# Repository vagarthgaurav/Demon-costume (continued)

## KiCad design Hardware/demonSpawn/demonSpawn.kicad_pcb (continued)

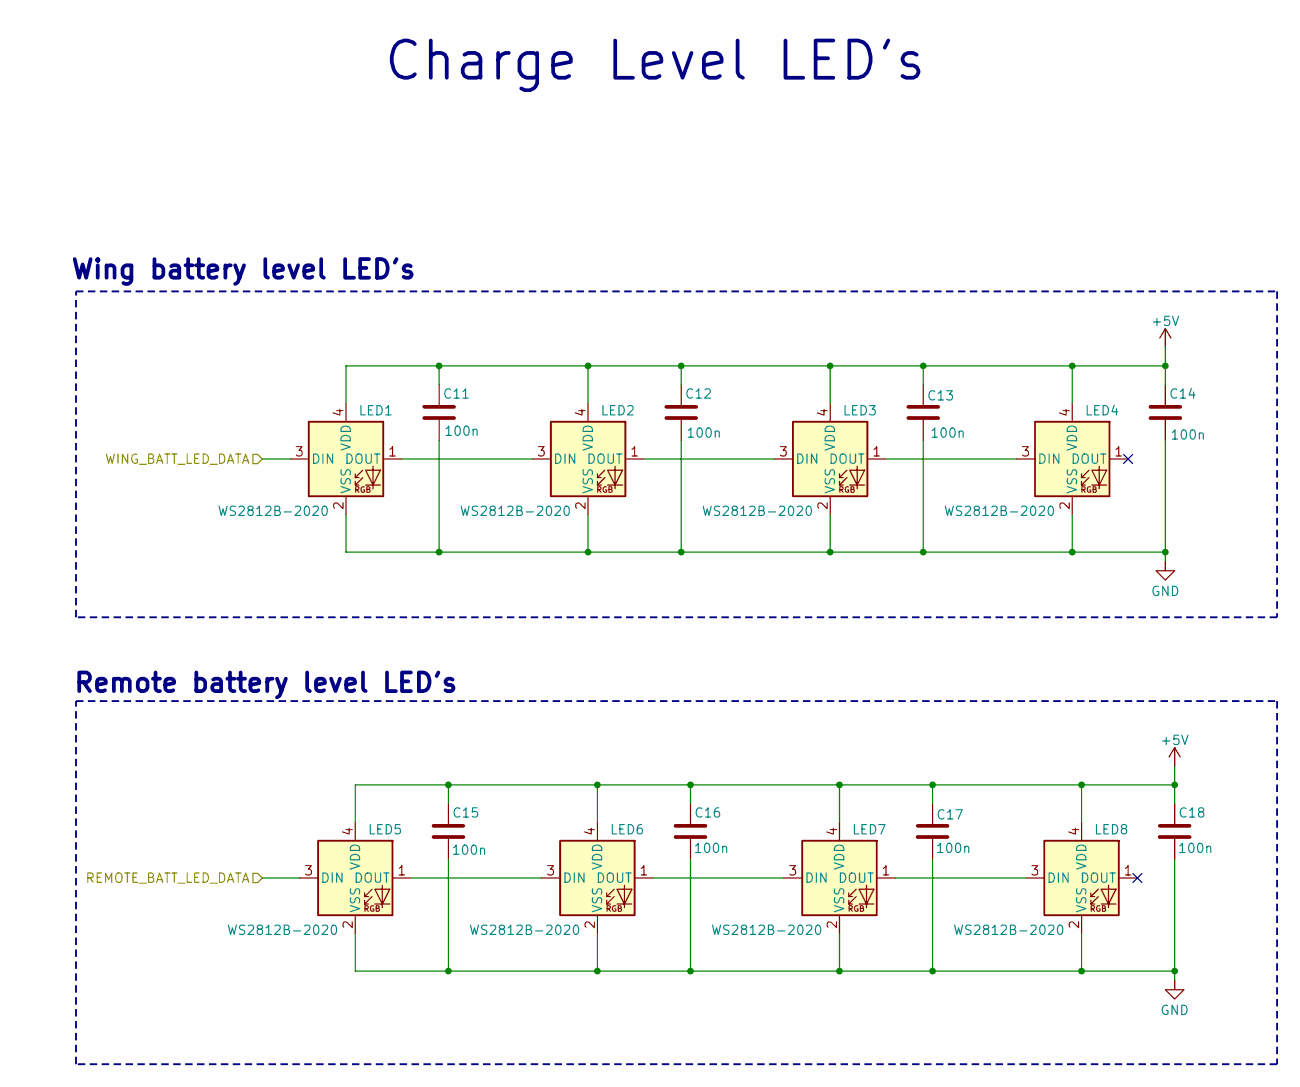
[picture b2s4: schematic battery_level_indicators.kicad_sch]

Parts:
C11, C12, C13, C14, C15, C16, C17, C18: 100n; C_0402_1005Metric
LED1, LED2, LED3, LED4, LED5, LED6, LED7, LED8: WS2812B-2020; LED_WS2812B-2020_PLCC4_2.0x2.0mm

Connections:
+5V: C11.2, C12.2, C13.2, C14.2, C15.2, C16.2, C17.2, C18.2, LED1.4 (VDD), LED2.4 (VDD), LED3.4 (VDD), LED4.4 (VDD), LED5.4 (VDD), LED6.4 (VDD), LED7.4 (VDD), LED8.4 (VDD); also elsewhere on the board
/Battery Level Indicators/REMOTE_BATT_LED_DATA: LED5.3 (DIN); also elsewhere on the board
/Battery Level Indicators/WING_BATT_LED_DATA: LED1.3 (DIN); also elsewhere on the board
GND: C11.1, C12.1, C13.1, C14.1, C15.1, C16.1, C17.1, C18.1, LED1.2 (VSS), LED2.2 (VSS), LED3.2 (VSS), LED4.2 (VSS), LED5.2 (VSS), LED6.2 (VSS), LED7.2 (VSS), LED8.2 (VSS); also elsewhere on the board
unnamed: LED1.1 (DOUT), LED2.3 (DIN)
unnamed: LED2.1 (DOUT), LED3.3 (DIN)
unnamed: LED3.1 (DOUT), LED4.3 (DIN)
unnamed: LED5.1 (DOUT), LED6.3 (DIN)
unnamed: LED6.1 (DOUT), LED7.3 (DIN)
unnamed: LED7.1 (DOUT), LED8.3 (DIN)

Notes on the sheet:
Charge Level LED's
Wing battery level LED's
Remote battery level LED's

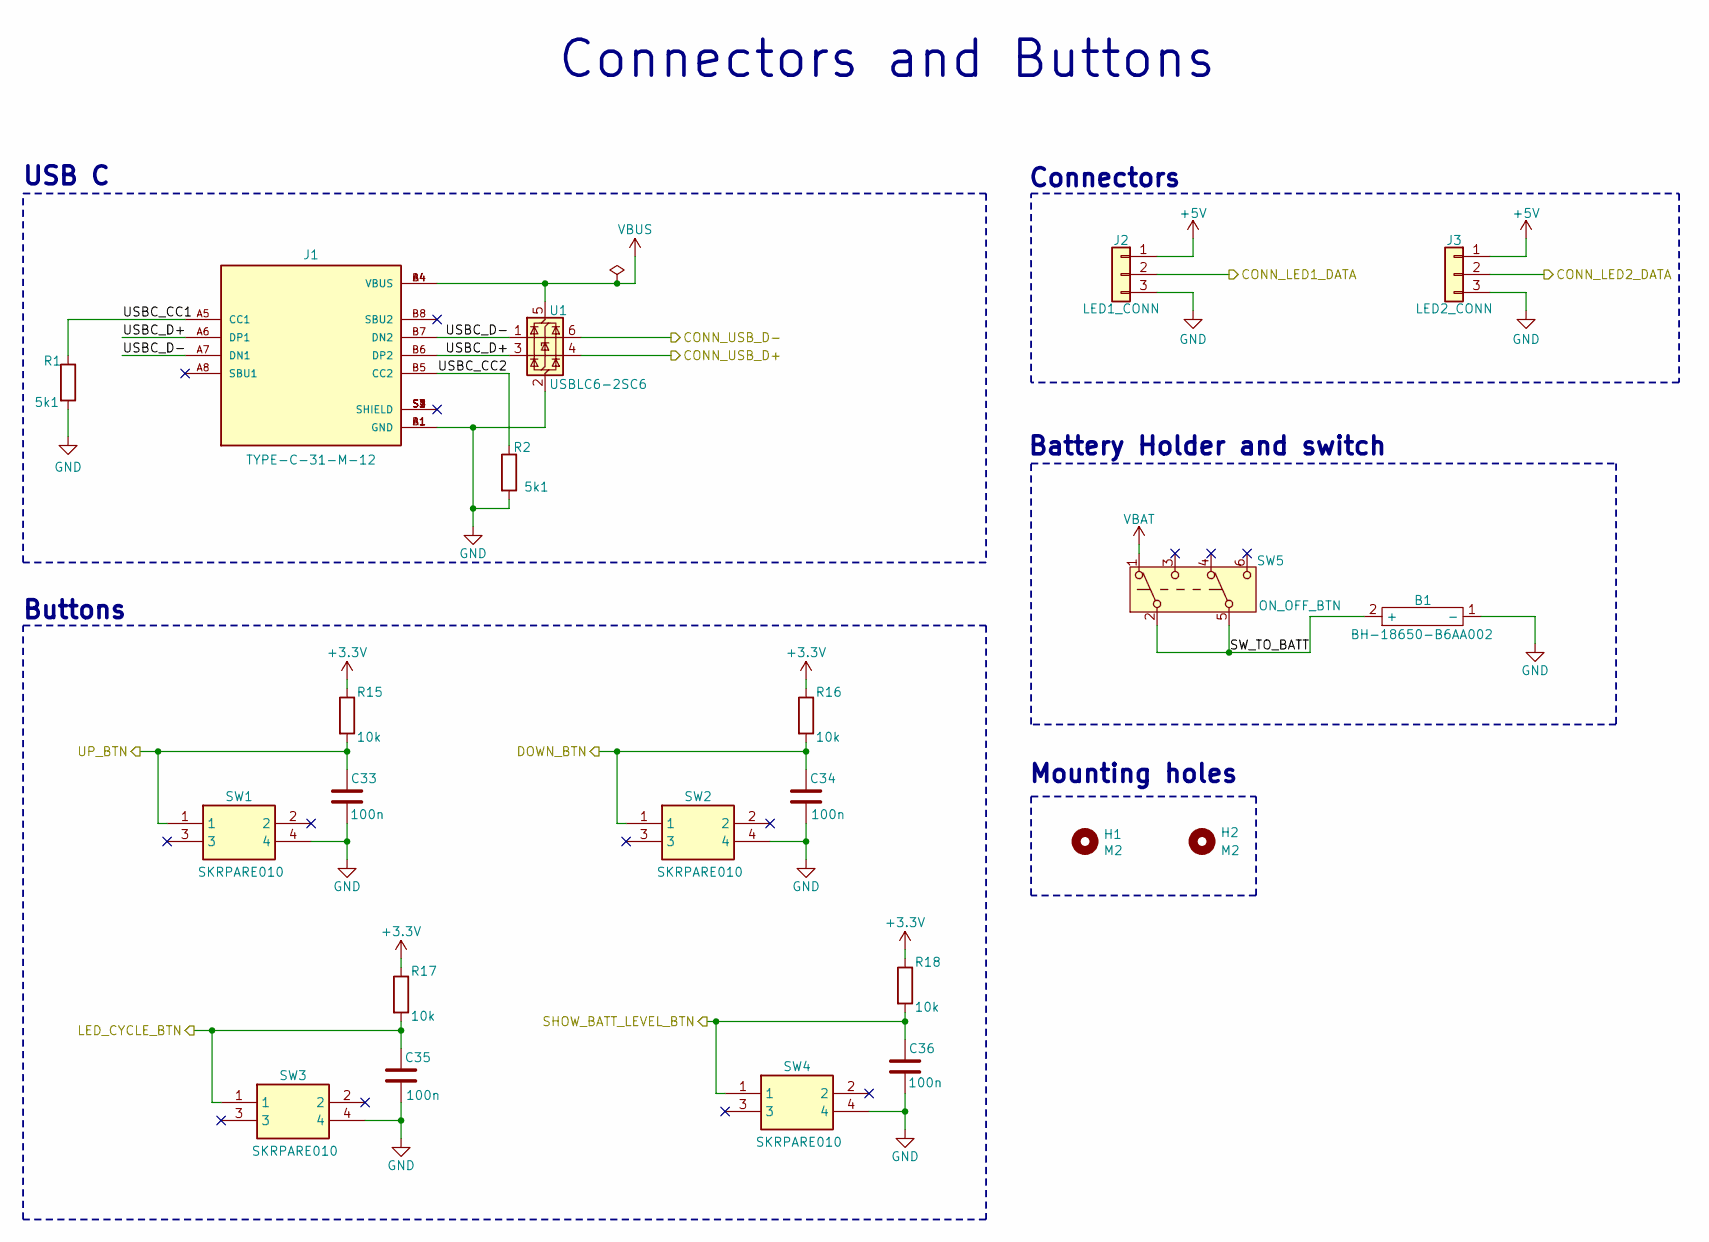
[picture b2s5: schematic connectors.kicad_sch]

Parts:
B1: BH-18650-B6AA002; BH-18650-B1BA002
C33, C34, C35, C36: 100n; C_0402_1005Metric
H1, H2: M2; MountingHole_2.2mm_M2_DIN965_Pad
J1: TYPE-C-31-M-12; HRO_TYPE-C-31-M-12; PARTREV 2020.12.08
J2: LED1_CONN; JST_PH_S3B-PH-K_1x03_P2.00mm_Horizontal
J3: LED2_CONN; JST_PH_S3B-PH-K_1x03_P2.00mm_Horizontal
R1, R2: 5k1; R_0402_1005Metric
R15, R16, R17, R18: 10k; R_0402_1005Metric
SW1, SW2, SW3, SW4: SKRPARE010; Mouser Part Number 688-SKRPARE010
SW5: ON_OFF_BTN; YIYUAN_YTSPS-22E59NL2
U1: USBLC6-2SC6; SOT-23-6

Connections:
+3.3V: R15.1, R16.1, R17.1, R18.1; also elsewhere on the board
+5V: J2.1, J3.1; also elsewhere on the board
/Battery Charger/CHG_USB_D+: U1.4 (I/O2); also elsewhere on the board
/Battery Charger/CHG_USB_D-: U1.6 (I/O1); also elsewhere on the board
/Connectors and Buttons/CONN_LED1_DATA: J2.2; also elsewhere on the board
/Connectors and Buttons/CONN_LED2_DATA: J3.2; also elsewhere on the board
/Connectors and Buttons/DOWN_BTN: C34.2, R16.2, SW2.1; also elsewhere on the board
/Connectors and Buttons/LED_CYCLE_BTN: C35.2, R17.2, SW3.1; also elsewhere on the board
/Connectors and Buttons/SHOW_BATT_LEVEL_BTN: C36.2, R18.2, SW4.1; also elsewhere on the board
/Connectors and Buttons/SW_TO_BATT: B1.2 (+), SW5.2 (B), SW5.5 (B)
/Connectors and Buttons/UP_BTN: C33.2, R15.2, SW1.1; also elsewhere on the board
/Connectors and Buttons/USBC_CC1: J1.A5 (CC1), R1.1
/Connectors and Buttons/USBC_CC2: J1.B5 (CC2), R2.1
/Connectors and Buttons/USBC_D+: J1.A6 (DP1), J1.B6 (DP2), U1.3 (I/O2)
/Connectors and Buttons/USBC_D-: J1.A7 (DN1), J1.B7 (DN2), U1.1 (I/O1)
GND: B1.1 (-), C33.1, C34.1, C35.1, C36.1, J1.A1 (GND), J1.B1 (GND), J2.3, J3.3, R1.2, R2.2, SW1.4, SW2.4, SW3.4, SW4.4, U1.2 (GND); also elsewhere on the board
VBAT: SW5.1 (A); also elsewhere on the board
VBUS: J1.A4 (VBUS), J1.B4 (VBUS), U1.5 (VBUS); also elsewhere on the board

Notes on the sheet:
USB C
Mounting holes
Battery Holder and switch
Buttons
Connectors and Buttons
Connectors

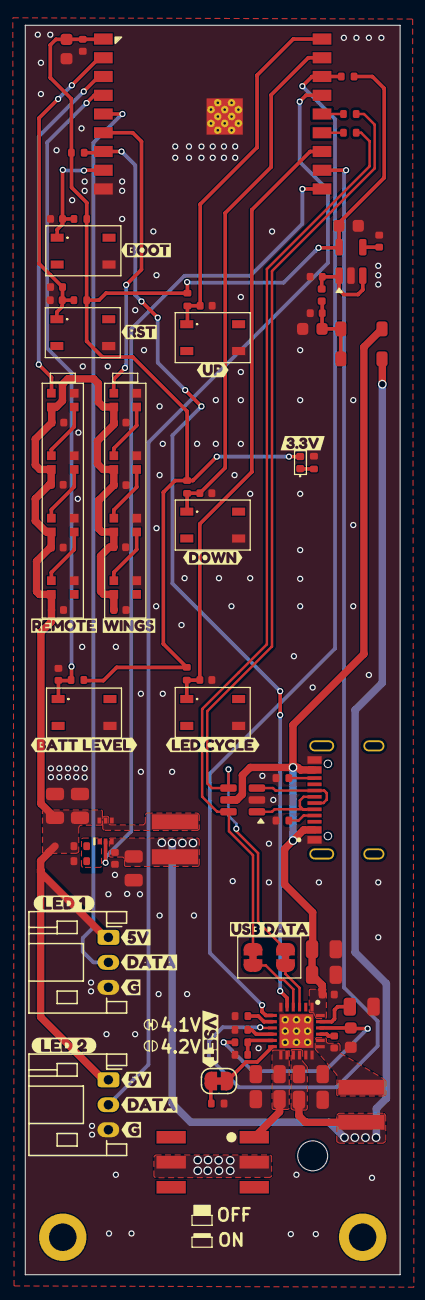
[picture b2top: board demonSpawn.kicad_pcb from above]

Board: 4 copper layers, 30.0 x 100.0 mm, 110 parts (1 on the bottom side), 52 nets.

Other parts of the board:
kibuzzard-691CA83A: G***; kibuzzard-691CA83A
kibuzzard-691CA85F: G***; kibuzzard-691CA85F
kibuzzard-691CA756, kibuzzard-691CA756#2: G***; kibuzzard-691CA756
kibuzzard-691CA769, kibuzzard-691CA769#2: G***; kibuzzard-691CA769
kibuzzard-691CAAF4: G***; kibuzzard-691CAAF4
kibuzzard-692B200D: G***; kibuzzard-692B200D
kibuzzard-692B208F: G***; kibuzzard-692B208F
kibuzzard-6926CBC7: G***; kibuzzard-6926CBC7
kibuzzard-6926CC00: G***; kibuzzard-6926CC00
kibuzzard-6926CC2A: G***; kibuzzard-6926CC2A
kibuzzard-6926CC4E: G***; kibuzzard-6926CC4E
kibuzzard-6926CC47: G***; kibuzzard-6926CC47
kibuzzard-6926CCE2: G***; kibuzzard-6926CCE2
kibuzzard-6926CCF6: G***; kibuzzard-6926CCF6
kibuzzard-6926CD00: G***; kibuzzard-6926CD00
kibuzzard-6926CD0F: G***; kibuzzard-6926CD0F
kibuzzard-6926CD20: G***; kibuzzard-6926CD20

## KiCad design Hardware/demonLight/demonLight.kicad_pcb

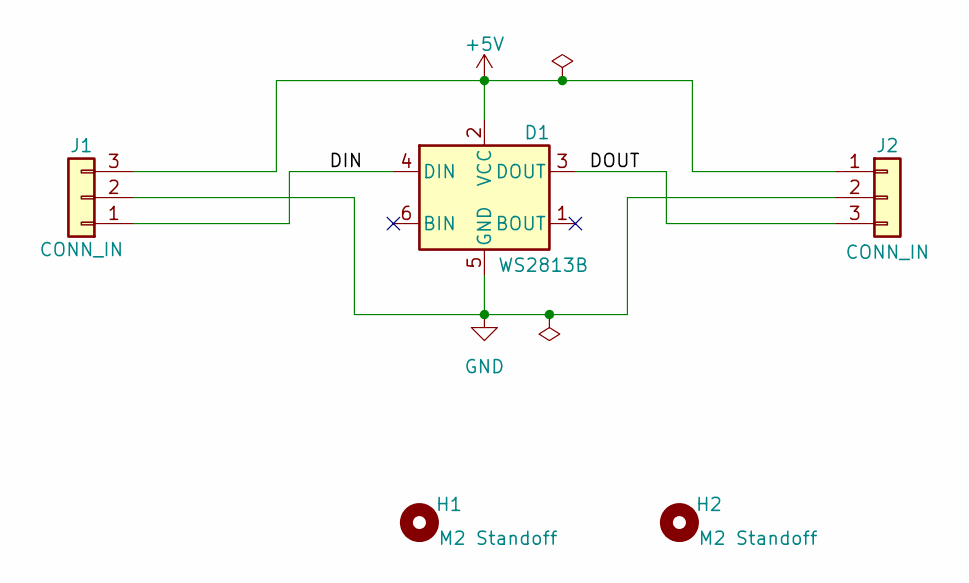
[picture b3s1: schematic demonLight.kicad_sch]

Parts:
D1: WS2813B; LED_WS2812_PLCC6_5.0x5.0mm_P1.6mm
H1, H2: M2 Standoff
J1, J2: CONN_IN; JST_PH_S3B-PH-K_1x03_P2.00mm_Horizontal

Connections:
+5V: D1.2 (VCC), J1.3, J2.1
/DIN: D1.4 (DIN), J1.1
/DOUT: D1.3 (DOUT), J2.3
GND: D1.5 (GND), J1.2, J2.2

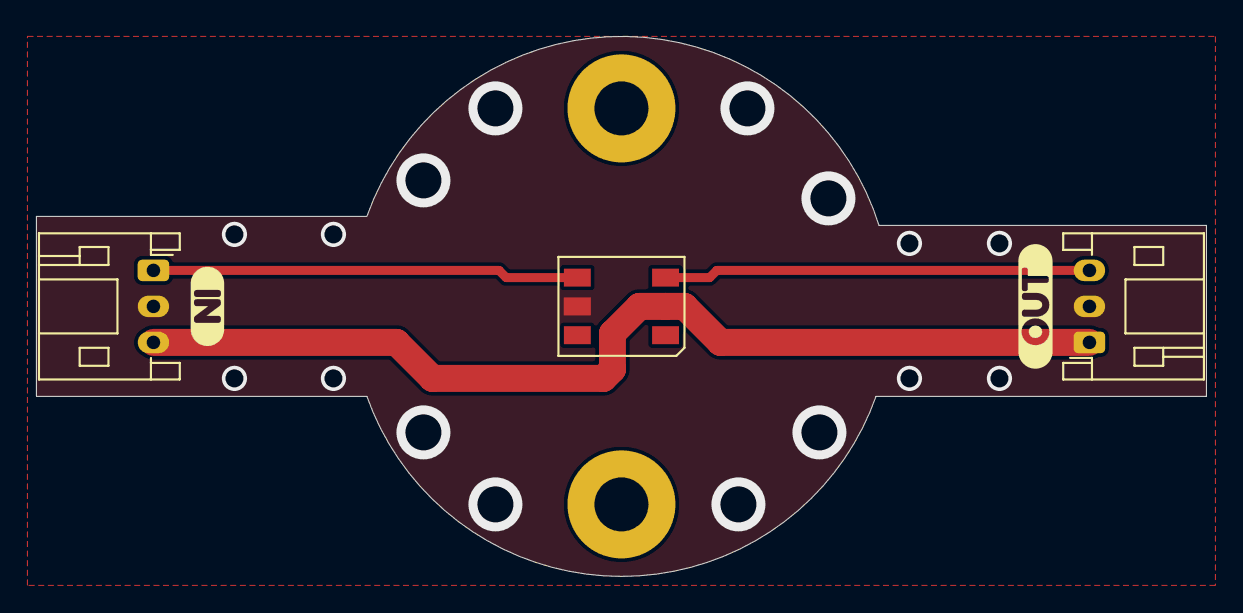
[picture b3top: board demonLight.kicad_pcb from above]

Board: 2 copper layers, 65.0 x 30.0 mm, 7 parts (0 on the bottom side), 4 nets.

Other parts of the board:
kibuzzard-692CA1C6: G***; kibuzzard-692CA1C6
kibuzzard-692CA1CF: G***; kibuzzard-692CA1CF

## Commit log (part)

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2025-12-09 feat: Initial commit
2025-12-09 docs: Add readme
2025-12-21 fix: Fix 5V connection
2026-01-05 doc: Add images
2026-01-05 doc: Resize image
2026-01-05 doc: Add schematic pdf
2026-01-08 feat: Add ibom.html
2026-01-16 Change resistors for leds
2026-01-17 Feat: Basic program
2026-06-21 chore: Add images to Git LFS
    Track images and PDFs with LFS, move images to images/ directory, and remove old root-level jpegs.
2026-06-21 fix: Fix typo in readme
2026-06-24 feat: Add demonBoard and demonRemote PlatformIO firmware projects
    Also update .gitignore to exclude .vscode and .history directories.
2026-06-24 Turn off the indicator leds when charging is disconnected.
2026-06-24 cleanup: Delete old arduino files
